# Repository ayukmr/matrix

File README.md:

# matrix

Charlieplexed LED matrix controlled by an ESP32-C6-MINI-1U.

## Schematic

## PCB

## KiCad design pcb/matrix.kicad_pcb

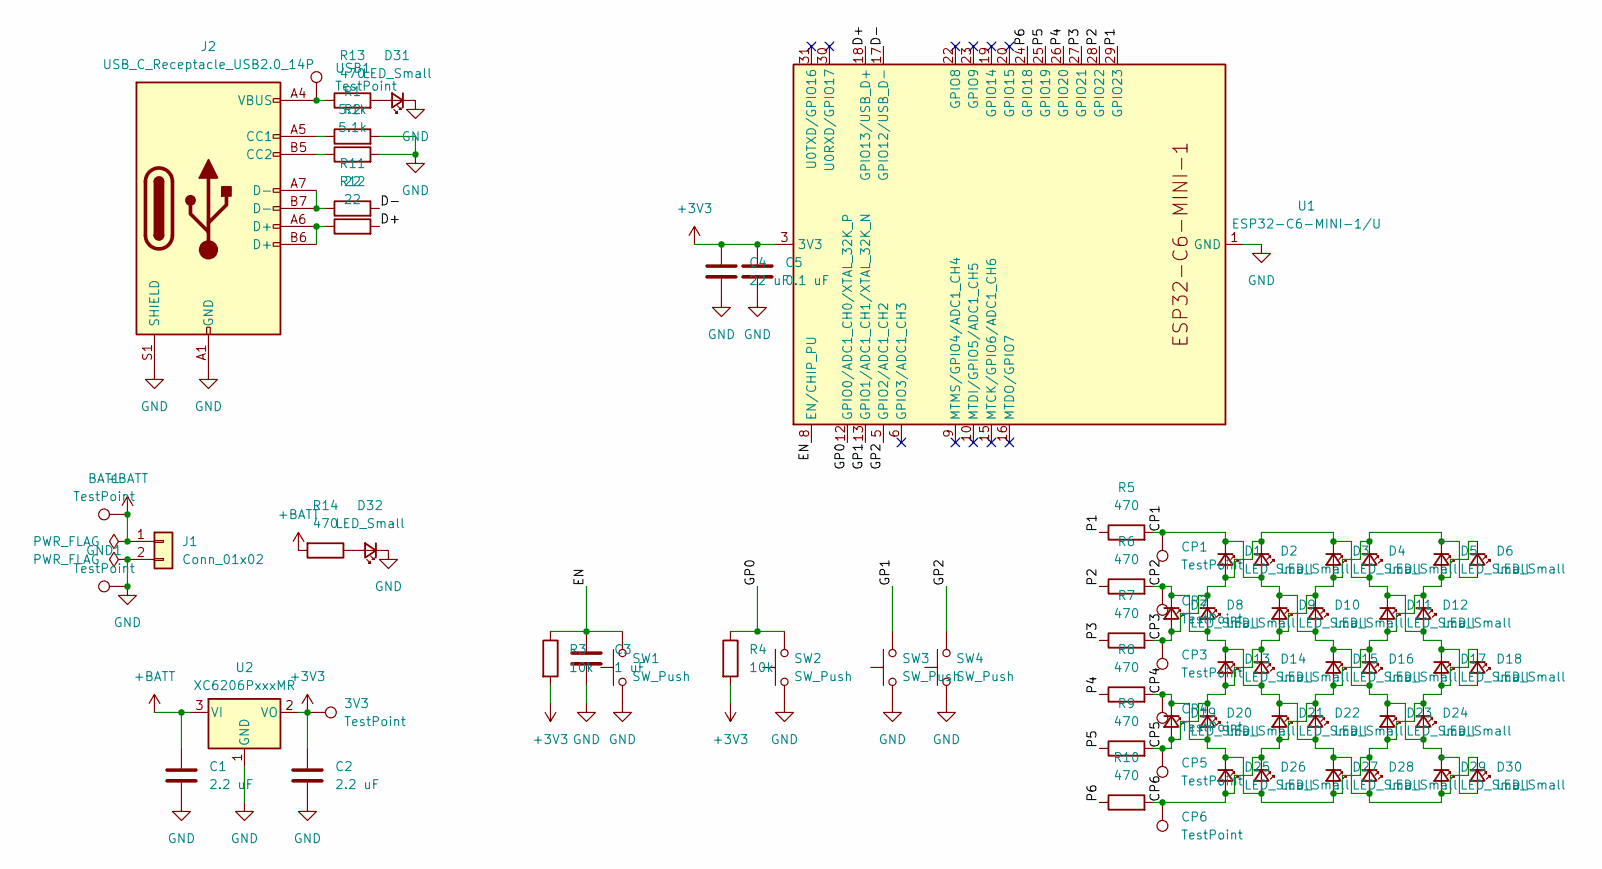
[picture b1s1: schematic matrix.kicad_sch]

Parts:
3V3: TestPoint; TestPoint_Pad_D1.0mm
BAT1: TestPoint; TestPoint_Pad_D1.0mm
C1, C2: 2.2 uF; C_0603_1608Metric
C3: 1 uF; C_0603_1608Metric
C4: 22 uF; C_0603_1608Metric
C5: 0.1 uF; C_0603_1608Metric
CP1, CP2, CP3, CP4, CP5, CP6: TestPoint; TestPoint_Pad_D1.0mm
D1, D2, D3, D4, D5, D6, D7, D8, D9, D10, D11, D12, D13, D14, D15, D16, D17, D18, D19, D20, D21, D22, D23, D24, D25, D26, D27, D28, D29, D30, D31, D32: LED_Small; LED_0603_1608Metric
GND1: TestPoint; TestPoint_Pad_D1.0mm
J1: Conn_01x02; JST_PH_B2B-PH-SM4-TB_1x02-1MP_P2.00mm_Vertical
J2: USB_C_Receptacle_USB2.0_14P; USB_C_Receptacle_HRO_TYPE-C-31-M-12
R1, R2: 5.1k; R_0603_1608Metric
R3, R4: 10k; R_0603_1608Metric
R5, R6, R7, R8, R9, R10, R13, R14: 470; R_0603_1608Metric
R11, R12: 22; R_0603_1608Metric
SW1, SW2, SW3, SW4: SW_Push; SW_SPST_TS-1088-xR020
U1: ESP32-C6-MINI-1/U; ESP32-C6-MINI-1U
U2: XC6206PxxxMR; SOT-23-3
USB1: TestPoint; TestPoint_Pad_D1.0mm

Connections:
+3V3: 3V3.1, C2.1, C4.1, C5.1, R3.2, R4.2, U1.3 (3V3), U2.2 (VO)
+BATT: BAT1.1, C1.1, J1.1, R14.2, U2.3 (VI); also elsewhere on the board
/CP1: CP1.1, D1.1 (K), D2.2 (A), D9.1 (K), D10.2 (A), D15.1 (K), D16.2 (A), D23.1 (K), D24.2 (A), D29.1 (K), D30.2 (A), R5.2
/CP2: CP2.1, D7.1 (K), D8.2 (A), D13.1 (K), D14.2 (A), D21.1 (K), D22.2 (A), D27.1 (K), D28.2 (A), D29.2 (A), D30.1 (K), R6.2
/CP3: CP3.1, D1.2 (A), D2.1 (K), D3.1 (K), D4.2 (A), D7.2 (A), D8.1 (K), D11.1 (K), D12.2 (A), D17.1 (K), D18.2 (A), R7.2
/CP4: CP4.1, D17.2 (A), D18.1 (K), D19.1 (K), D20.2 (A), D23.2 (A), D24.1 (K), D25.1 (K), D26.2 (A), D27.2 (A), D28.1 (K), R8.2
/CP5: CP5.1, D3.2 (A), D4.1 (K), D5.1 (K), D6.2 (A), D9.2 (A), D10.1 (K), D13.2 (A), D14.1 (K), D19.2 (A), D20.1 (K), R9.2
/CP6: CP6.1, D5.2 (A), D6.1 (K), D11.2 (A), D12.1 (K), D15.2 (A), D16.1 (K), D21.2 (A), D22.1 (K), D25.2 (A), D26.1 (K), R10.2
/D+: R12.2, U1.18 (GPIO13/USB_D+)
/D-: R11.2, U1.17 (GPIO12/USB_D-)
/EN: C3.1, R3.1, SW1.2, U1.8 (EN/CHIP_PU)
/GP0: R4.1, SW2.2, U1.12 (GPIO0/ADC1_CH0/XTAL_32K_P)
/GP1: SW3.2, U1.13 (GPIO1/ADC1_CH1/XTAL_32K_N)
/GP2: SW4.2, U1.5 (GPIO2/ADC1_CH2)
/P1: R5.1, U1.29 (GPIO23)
/P2: R6.1, U1.28 (GPIO22)
/P3: R7.1, U1.27 (GPIO21)
/P4: R8.1, U1.26 (GPIO20)
/P5: R9.1, U1.25 (GPIO19)
/P6: R10.1, U1.24 (GPIO18)
GND: C1.2, C2.2, C3.2, C4.2, C5.2, D31.1 (K), D32.1 (K), GND1.1, J1.2, J2.A1 (GND), J2.A12 (GND), J2.B1 (GND), J2.B12 (GND), J2.S1 (SHIELD), R1.2, R2.2, SW1.1, SW2.1, SW3.1, SW4.1, U1.1 (GND), U1.2 (GND), U1.11 (GND), U1.14 (GND), U1.36 (GND), U1.37 (GND), U1.38 (GND), U1.39 (GND), U1.40 (GND), U1.41 (GND), U1.42 (GND), U1.43 (GND), U1.44 (GND), U1.45 (GND), U1.46 (GND), U1.47 (GND), U1.48 (GND), U1.49 (GND), U1.50 (GND), U1.51 (GND), U1.52 (GND), U1.53 (GND), U2.1 (GND); also elsewhere on the board
unnamed: D31.2 (A), R13.2
unnamed: D32.2 (A), R14.1
unnamed: J2.A5 (CC1), R1.1
unnamed: J2.B5 (CC2), R2.1
unnamed: J2.A6 (D+), J2.B6 (D+), R12.1
unnamed: J2.A7 (D-), J2.B7 (D-), R11.1
unnamed 27: J2.A4 (VBUS), J2.A9 (VBUS), J2.B4 (VBUS), J2.B9 (VBUS), R13.1, USB1.1; also elsewhere on the board

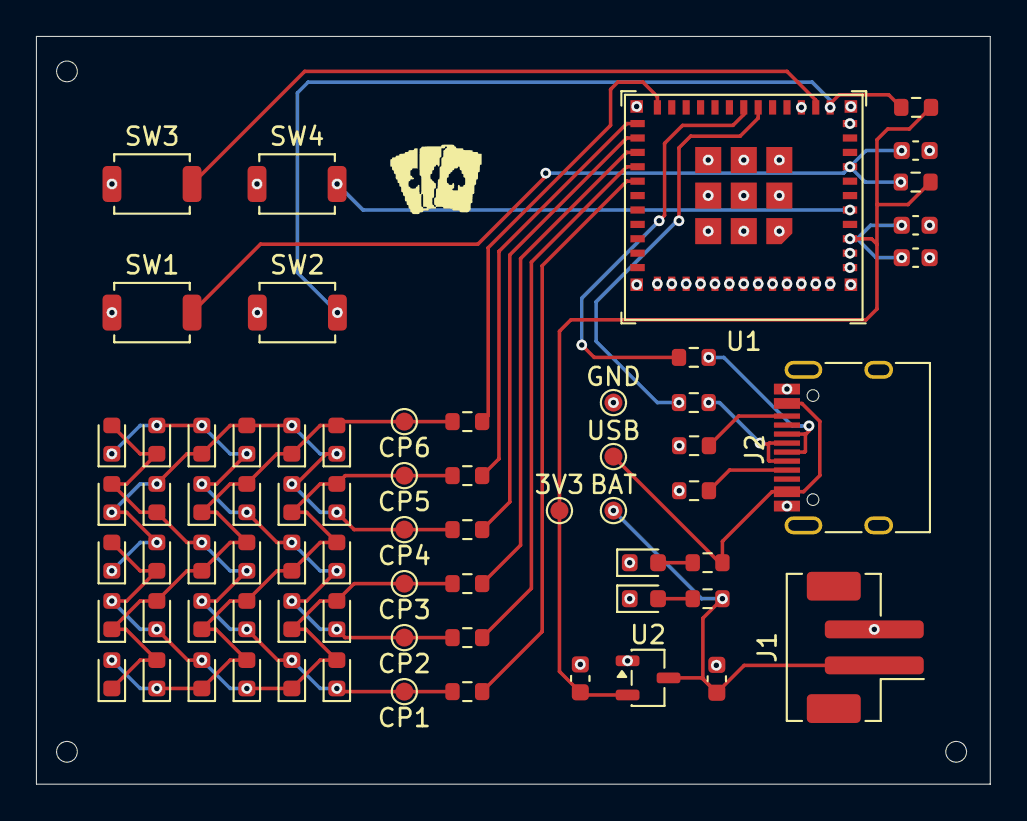
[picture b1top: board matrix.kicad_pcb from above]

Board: 2 copper layers, 53.0 x 41.5 mm, 69 parts (0 on the bottom side), 28 nets.

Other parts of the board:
BAT: TestPoint; TestPoint_Pad_D1.0mm
GND: TestPoint; TestPoint_Pad_D1.0mm
USB: TestPoint; TestPoint_Pad_D1.0mm

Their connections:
+BATT: BAT.1; also elsewhere on the board
GND: GND.1; also elsewhere on the board
unnamed 27: USB.1; also elsewhere on the board

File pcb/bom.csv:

Reference,Qty,Value,Footprint,Datasheet,LCSC Part #,Link,Price
"C1,C2",2,2.2 µF,Capacitor_SMD:C_0603_1608Metric,~,C23630,https://jlcpcb.com/partdetail/24366-CL10A225KO8NNNC/C23630,0.0055
C3,1,1 µF,Capacitor_SMD:C_0603_1608Metric,~,C15849,https://jlcpcb.com/partdetail/16531-CL10A105KB8NNNC/C15849,0.0048
C4,1,22 µF,Capacitor_SMD:C_0603_1608Metric,~,C59461,https://jlcpcb.com/partdetail/60514-CL10A226MQ8NRNC/C59461,0.0083
C5,1,0.1 µF,Capacitor_SMD:C_0603_1608Metric,~,C14663,https://jlcpcb.com/partdetail/YAGEO-CC0603KRX7R9BB104/C14663,0.0024
"D1,D2,D3,D4,D5,D6,D7,D8,D9,D10,D11,D12,D13,D14,D15,D16,D17,D18,D19,D20,D21,D22,D23,D24,D25,D26,D27,D28,D29,D30,D31,D32",32,LED_Small,LED_SMD:LED_0603_1608Metric,~,C2286,https://jlcpcb.com/partdetail/Hubei_KENTOElec-KT0603R/C2286,0.0058
J1,1,Conn_01x02,Connector_JST:JST_PH_B2B-PH-SM4-TB_1x02-1MP_P2.00mm_Vertical,~,C160352,https://jlcpcb.com/partdetail/JST-B2B_PH_SM4_TB_LF_SN/C160352,0.394
J2,1,USB_C_Receptacle_USB2.0_14P,Connector_USB:USB_C_Receptacle_HRO_TYPE-C-31-M-12,https://www.usb.org/sites/default/files/documents/usb_type-c.zip,C165948,https://jlcpcb.com/partdetail/Korean_HropartsElec-TYPE_C_31_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,0.1731
"R1,R2",2,5.1k Ω,Resistor_SMD:R_0603_1608Metric,~,C25905,https://jlcpcb.com/partdetail/26648-0402WGF5101TCE/C25905,0.0006
"R3,R4",2,10k Ω,Resistor_SMD:R_0603_1608Metric,~,C25744,https://jlcpcb.com/partdetail/26487-0402WGF1002TCE/C25744,0.0006
"R5,R6,R7,R8,R9,R10,R13,R14",8,470 Ω,Resistor_SMD:R_0603_1608Metric,~,C25117,https://jlcpcb.com/partdetail/25860-0402WGF4700TCE/C25117,0.0006
"R11,R12",2,22 Ω,Resistor_SMD:R_0603_1608Metric,~,C25092,https://jlcpcb.com/partdetail/25835-0402WGF220JTCE/C25092,0.0006
"SW1,SW2,SW3,SW4",4,SW_Push,Button_Switch_SMD:SW_SPST_PTS810,~,C720477,https://jlcpcb.com/partdetail/XUNPU-TS_1088AR02016/C720477,0.0434
U1,1,ESP32-C6-MINI-1U,RF_Module:ESP32-C6-MINI-1U,https://www.espressif.com/sites/default/files/documentation/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,C20627095,https://jlcpcb.com/partdetail/22039339-ESP32_C6_MINI_1UH4/C20627095,4.8423
U2,1,XC6206PxxxMR,Package_TO_SOT_SMD:SOT-23-3,https://www.torexsemi.com/file/xc6206/XC6206.pdf,C5446,https://jlcpcb.com/partdetail/TorexSemicon-XC6206P332MRG/C5446,0.0905

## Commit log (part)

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2025-12-30 Initialize repo
2025-12-31 Refill zone
2025-12-31 Update gitignore
2025-12-31 Update silkscreen
2025-12-31 Fix incorrect voltage
2025-12-31 Update parts
2025-12-31 Update README BOM
2026-01-02 Replace components
2026-01-03 Update to C6-MINI
2026-01-03 Organize schematic
2026-01-14 Update BOM
2026-02-06 Remove BOM
